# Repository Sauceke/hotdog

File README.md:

# Project moved to https://codeberg.org/Sauceke/hotdog

This repository is preserved only to keep old links working. All development will take place on
Codeberg from now on.

Read more about why this happened here:

https://www.404media.co/github-ban-suspension-adult-modding-games-illusion/

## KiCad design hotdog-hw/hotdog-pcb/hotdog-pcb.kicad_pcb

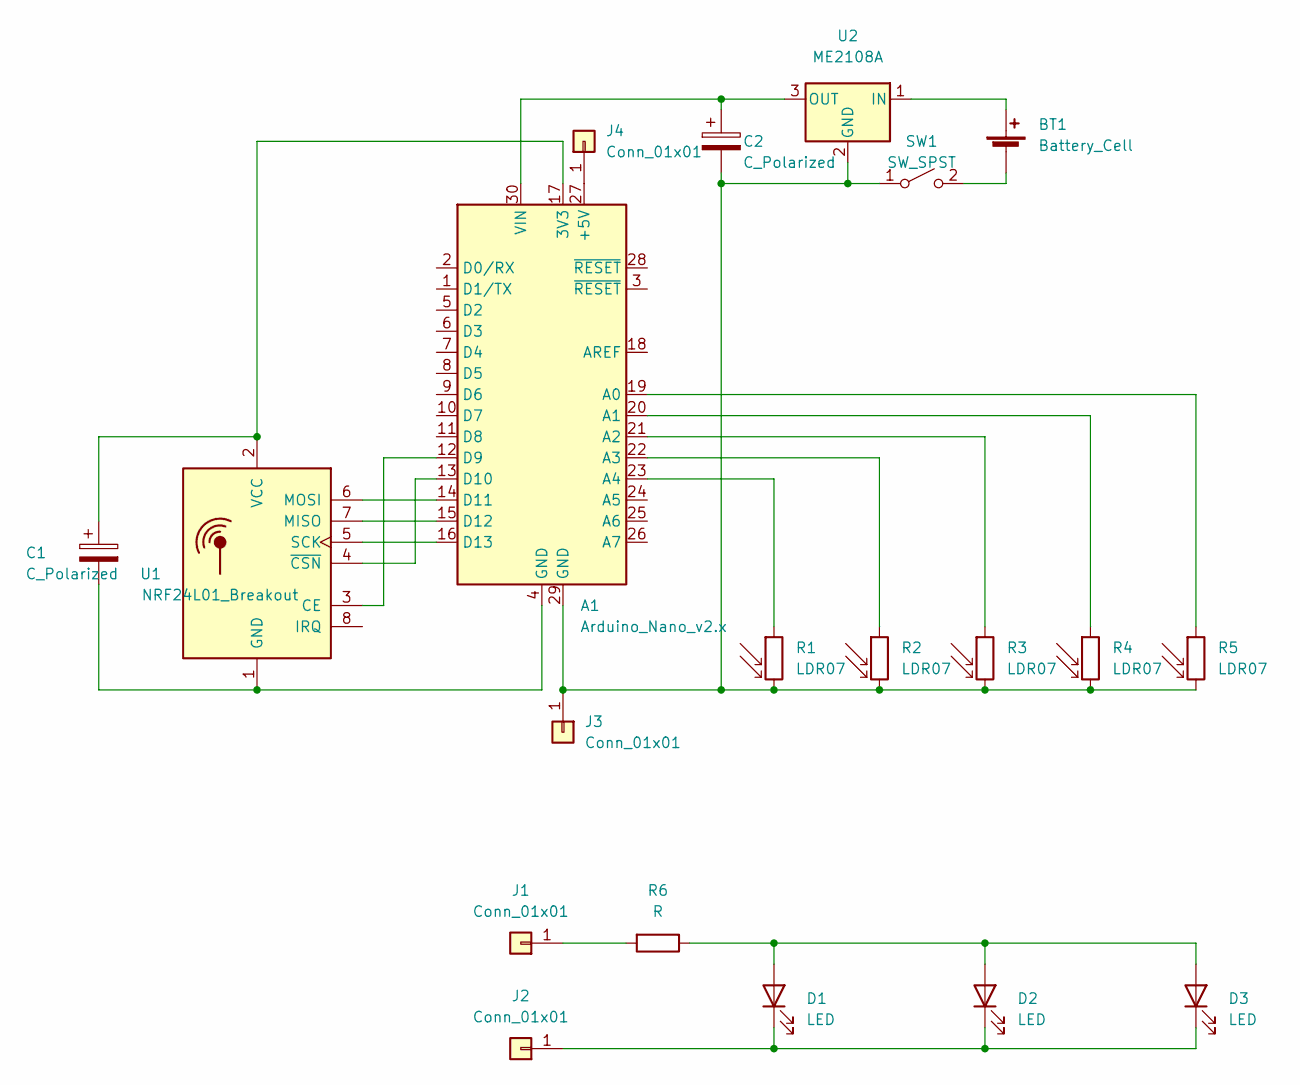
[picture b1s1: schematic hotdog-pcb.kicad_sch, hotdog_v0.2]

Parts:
A1: Arduino_Nano_v2.x; Arduino_Nano
BT1: Battery_Cell; BatteryHolder_Keystone_2466_1xAAA
C1, C2: C_Polarized; CP_Radial_D6.3mm_P2.50mm
D1, D2, D3: LED; LED_D5.0mm
J1, J2, J3, J4: Conn_01x01; SolderWire-0.1sqmm_1x01_D0.4mm_OD1mm
R1, R2, R3, R4, R5: LDR07; R_LDR_5.1x4.3mm_P3.4mm_Vertical
R6: R; R_Axial_DIN0204_L3.6mm_D1.6mm_P5.08mm_Horizontal
SW1: SW_SPST
U1: NRF24L01_Breakout; nRF24L01_Breakout
U2: ME2108A; Converter_DCDC_RECOM_R-78E-0.5_THT

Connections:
unnamed: A1.4 (GND), C1.2, U1.1 (GND)
unnamed: A1.12 (D9), U1.3 (CE)
unnamed: A1.13 (D10), U1.4 (~CSN)
unnamed: A1.14 (D11), U1.6 (MOSI)
unnamed: A1.15 (D12), U1.7 (MISO)
unnamed: A1.16 (D13), U1.5 (SCK)
unnamed: A1.17 (3V3), C1.1, U1.2 (VCC)
unnamed: A1.19 (A0), R5.1
unnamed: A1.20 (A1), R4.1
unnamed: A1.21 (A2), R3.1
unnamed: A1.22 (A3), R2.1
unnamed: A1.23 (A4), R1.1
unnamed: A1.27 (+5V), J4.1
unnamed: A1.29 (GND), C2.2, J3.1, R1.2, R2.2, R3.2, R4.2, R5.2, SW1.1 (A), U2.2 (GND)
unnamed: A1.30 (VIN), C2.1, U2.3 (OUT)
unnamed: BT1.1 (+), U2.1 (IN)
unnamed: BT1.2 (-), SW1.2 (B)
unnamed: D1.1 (K), D2.1 (K), D3.1 (K), J2.1
unnamed: D1.2 (A), D2.2 (A), D3.2 (A), R6.1
unnamed: J1.1, R6.2

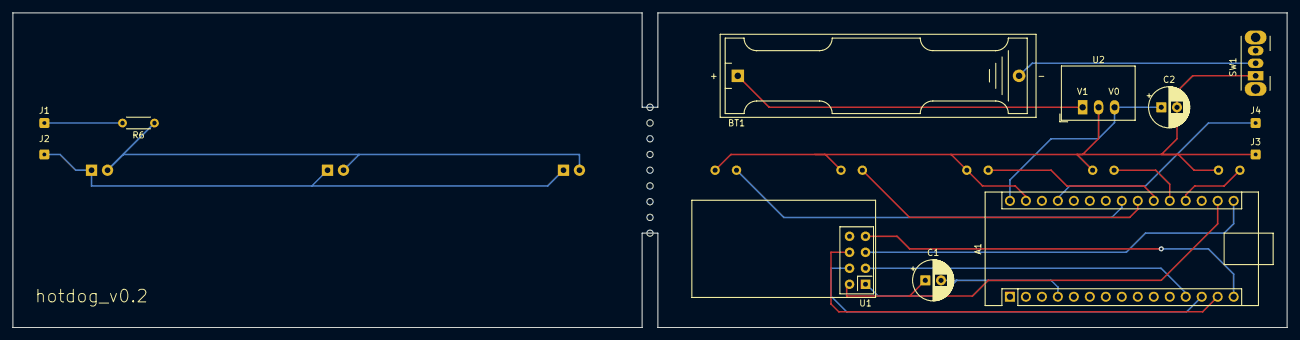
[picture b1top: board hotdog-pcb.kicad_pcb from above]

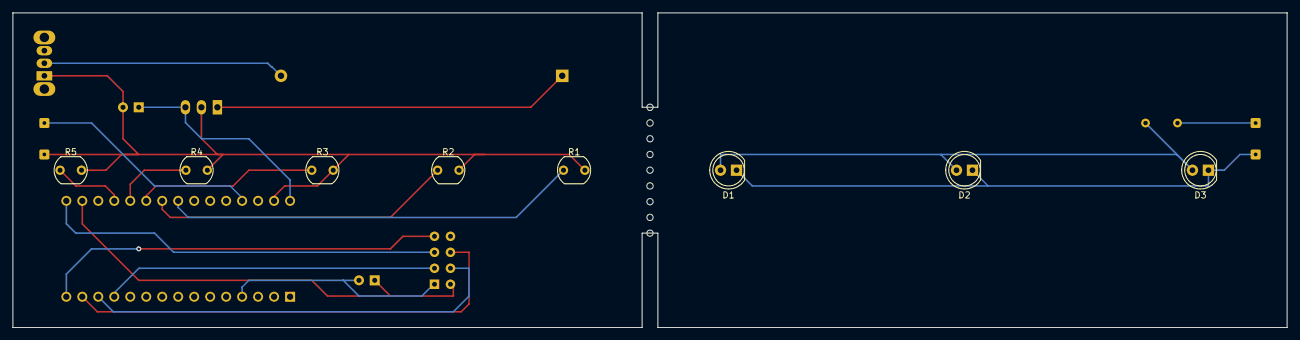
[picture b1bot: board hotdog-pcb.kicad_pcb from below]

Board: 2 copper layers, 202.5 x 50.0 mm, 20 parts (8 on the bottom side), 20 nets.

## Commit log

2022-02-17 Add circuit diagram
2022-02-17 Add release job
2022-02-17 svg no longer needed, circuitdiagram is FOSS
2022-02-18 Add estimated price
2022-03-31 Fix stl links
2022-04-26 Add PCB files
2022-04-28 Simplify PCB
2022-04-28 Smooth out a few rough spots in pcb
2022-04-29 Learned my lesson about PCB pooling
2022-05-03 Upload images for assembly guide
2022-05-03 github, your relative path resolution algorithm is broken af
2022-05-04 draw the rest of the fucking owl
2022-05-20 BLE broadcasting, convert output to T-code
2022-05-20 Render PCBs in release job
2022-05-20 Add arduino libraries to release job
2022-05-20 Haha fuck yaml
2022-05-20 shut up
2022-05-20 you said it was optional you liar
2022-05-21 try to setup kibot
2022-05-21 yml...
2022-05-21 yml......
2022-05-21 remove intermediate kicad outputs
2022-05-21 what do you mean permission denied
2022-05-21 export selected layers
2022-05-21 whatever i'll just list the layers manually
2022-05-21 Add hex files to release
2022-05-21 do i need =
2022-05-21 guess its just nano then
2022-05-21 nah let's go with nano every
2022-05-21 Zip nano every binaries
2022-05-21 Fix compatibility with AVR boards
2022-05-21 Wireless version assembly guide
2022-05-22 Add photos and instructions for wireless assembly
2022-05-22 Add xloader image
2022-05-26 better cropping on some images
2022-06-26 Add server
2022-06-30 fix server args off by one
2022-06-30 Include server in release
2022-06-30 usual gh actions fuckery
2022-06-30 come on
2022-06-30 Fix server assets path
2022-06-30 Automated server versioning
2022-07-01 Sorted Files
2022-07-01 Reworked README
2022-07-01 Formatted Wired Documentation
2022-07-01 Formatted Most Of Wireless
2022-07-01 Finished Formatting Wireless
2022-07-01 Added Basic Logo
2022-07-01 Fixed Up Workflows
2022-07-01 On Request : Moved Assembly Links To README
2022-07-01 On Request : Relatively Sized Images
2022-07-02 On Request : Trailing <br> 🠖 2 x Space
2022-07-02 Fix server build job
2022-07-02 Set theme jekyll-theme-midnight
2022-07-02 Set md flavor to gfm
2022-07-02 Set theme jekyll-theme-hacker
2022-07-03 Set theme jekyll-theme-modernist
2023-05-06 fix links
2026-01-07 Moved
